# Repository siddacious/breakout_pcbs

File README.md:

neopixel_nano_strip
------------------
**Status**: Tested working

A snappable strip of 5 neopixel nanos. Once snapped they can be chained together and sewn to something.

uson_wson_breakout
-----------------
**Status**: **_Untested_**

A double sided breakout for Windbond QSPI flash chips. 2x3mm and 4x3mm USON on one side an 5x6mm WSON on the other.

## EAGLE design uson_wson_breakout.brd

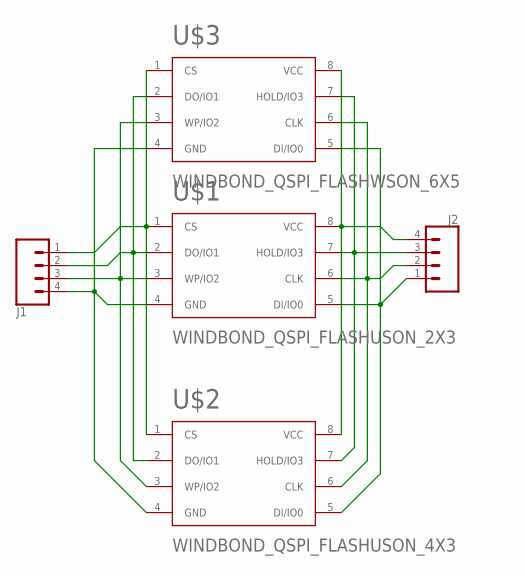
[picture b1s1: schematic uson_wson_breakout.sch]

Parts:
J1, J2: CONN_041X04_NO_SILK; 1X04_NO_SILK
U$1: WINDBOND_QSPI_FLASHUSON_2X3; USON_2X3MM
U$2: WINDBOND_QSPI_FLASHUSON_4X3; USON_4X3MM
U$3: WINDBOND_QSPI_FLASHWSON_6X5; WSON_6X5MM

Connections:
3V3: J2.4, U$1.8 (VCC), U$2.8 (VCC), U$3.8 (VCC)
CLK: J2.2, U$1.6 (CLK), U$2.6 (CLK), U$3.6 (CLK)
CS: J1.1, U$1.1 (CS), U$2.1 (CS), U$3.1 (CS)
DI/IO0: J2.1, U$1.5 (DI/IO0), U$2.5 (DI/IO0), U$3.5 (DI/IO0)
DO/IO1: J1.2, U$1.2 (DO/IO1), U$2.2 (DO/IO1), U$3.2 (DO/IO1)
GND: J1.4, U$1.4 (GND), U$2.4 (GND), U$3.4 (GND)
HOLD/IO3: J2.3, U$1.7 (HOLD/IO3), U$2.7 (HOLD/IO3), U$3.7 (HOLD/IO3)
WP/IO2: J1.3, U$1.3 (WP/IO2), U$2.3 (WP/IO2), U$3.3 (WP/IO2)

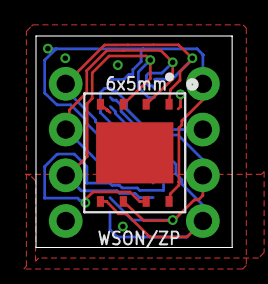
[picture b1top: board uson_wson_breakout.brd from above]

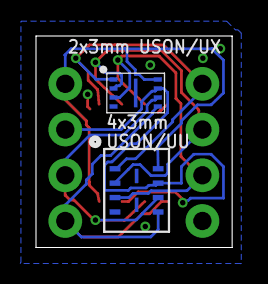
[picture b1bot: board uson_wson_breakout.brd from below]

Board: 2 copper layers, 10.9 x 11.8 mm, 5 parts (2 on the bottom side), 8 nets.

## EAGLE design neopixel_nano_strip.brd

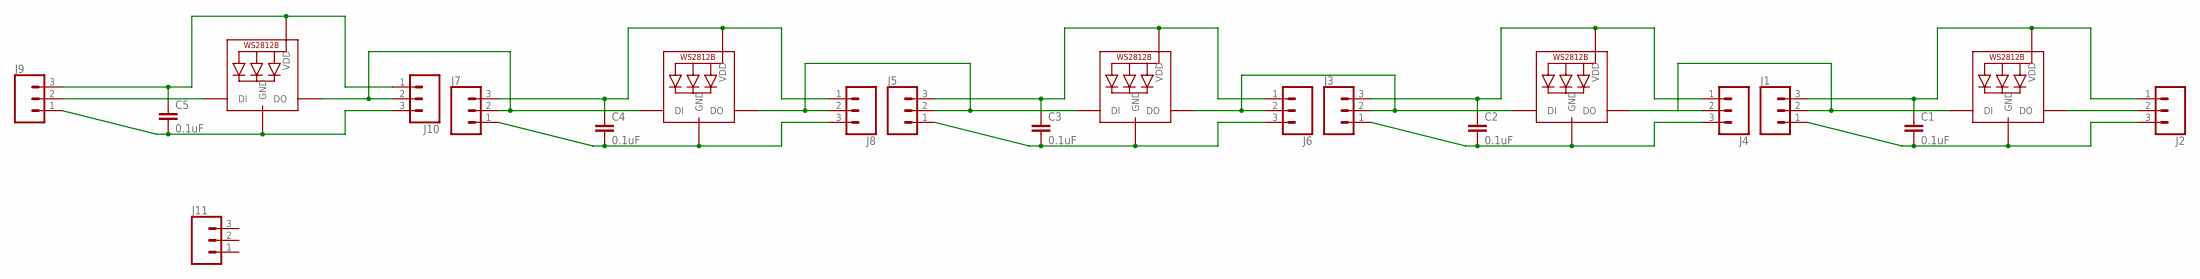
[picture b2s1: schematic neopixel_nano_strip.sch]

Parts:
C1, C2, C3, C4, C5: 0.1uF; 0603
J1, J2, J3, J4, J5, J6, J7, J8, J9, J10, J11: CONN_031X03_NO_SILK; 1X03_NO_SILK
LED1, LED2, LED3, LED4, LED5: WS2812BNANO; NEOPIXEL_NANO

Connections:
DIN4: J9.2, LED5.P$3 (DI)
DOUT: J2.2, LED1.P$1 (DO)
DOUT1: J1.2, J4.2, LED1.P$3 (DI), LED2.P$1 (DO)
DOUT2: J3.2, J6.2, LED2.P$3 (DI), LED3.P$1 (DO)
DOUT3: J5.2, J8.2, LED3.P$3 (DI), LED4.P$1 (DO)
DOUT4: J7.2, J10.2, LED4.P$3 (DI), LED5.P$1 (DO)
GND: C1.2, C2.2, C3.2, C4.2, C5.2, J1.1, J2.3, J3.1, J4.3, J5.1, J6.3, J7.1, J8.3, J9.1, J10.3, LED1.P$2 (GND), LED2.P$2 (GND), LED3.P$2 (GND), LED4.P$2 (GND), LED5.P$2 (GND)
VCC: C1.1, C2.1, C3.1, C4.1, C5.1, J1.3, J2.1, J3.3, J4.1, J5.3, J6.1, J7.3, J8.1, J9.3, J10.1, LED1.P$4 (VDD), LED2.P$4 (VDD), LED3.P$4 (VDD), LED4.P$4 (VDD), LED5.P$4 (VDD)

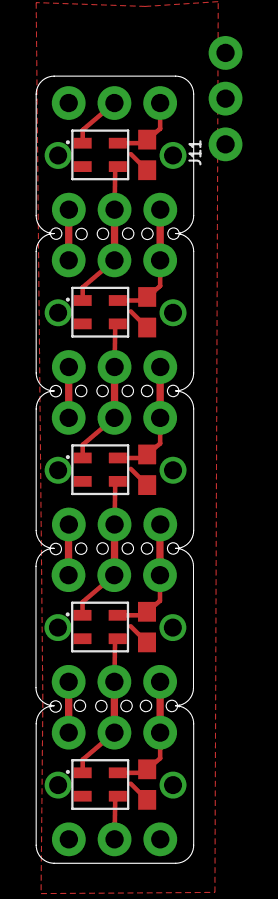
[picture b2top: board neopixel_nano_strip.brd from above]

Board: 2 copper layers, 8.8 x 43.7 mm, 21 parts (0 on the bottom side), 8 nets.

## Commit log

2017-11-16 a fresh batch of treats
2017-11-16 Fixing README typos

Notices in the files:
parts and their libraries:
SparkFun-Capacitors: Licensing: Creative Commons ShareAlike 4.0 International - https://creativecommons.org/licenses/by-sa/4.0
